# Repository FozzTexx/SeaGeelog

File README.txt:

SeaGeelog: CGA/RGBI to analog converter board
Copyright 2014 by Chris Osborn
http://insentricity.com/a.cl/219

This work is licensed under a Creative Commons Attribution-ShareAlike
4.0 International License.
http://creativecommons.org/licenses/by-sa/4.0/

This circuit is designed to convert a standard TTL level CGA/RGBI
signal to analog RGB voltages. I have tested it with the output from
my Commodore 128. It does *not* do any scan doubling or conversion to
VGA frequences. The output will still be at the CGA/RGBI frequencies
which works with old Apple or arcade monitors. I'm using a GBS-8200
clone to convert the SeaGeelog output to a VGA signal.

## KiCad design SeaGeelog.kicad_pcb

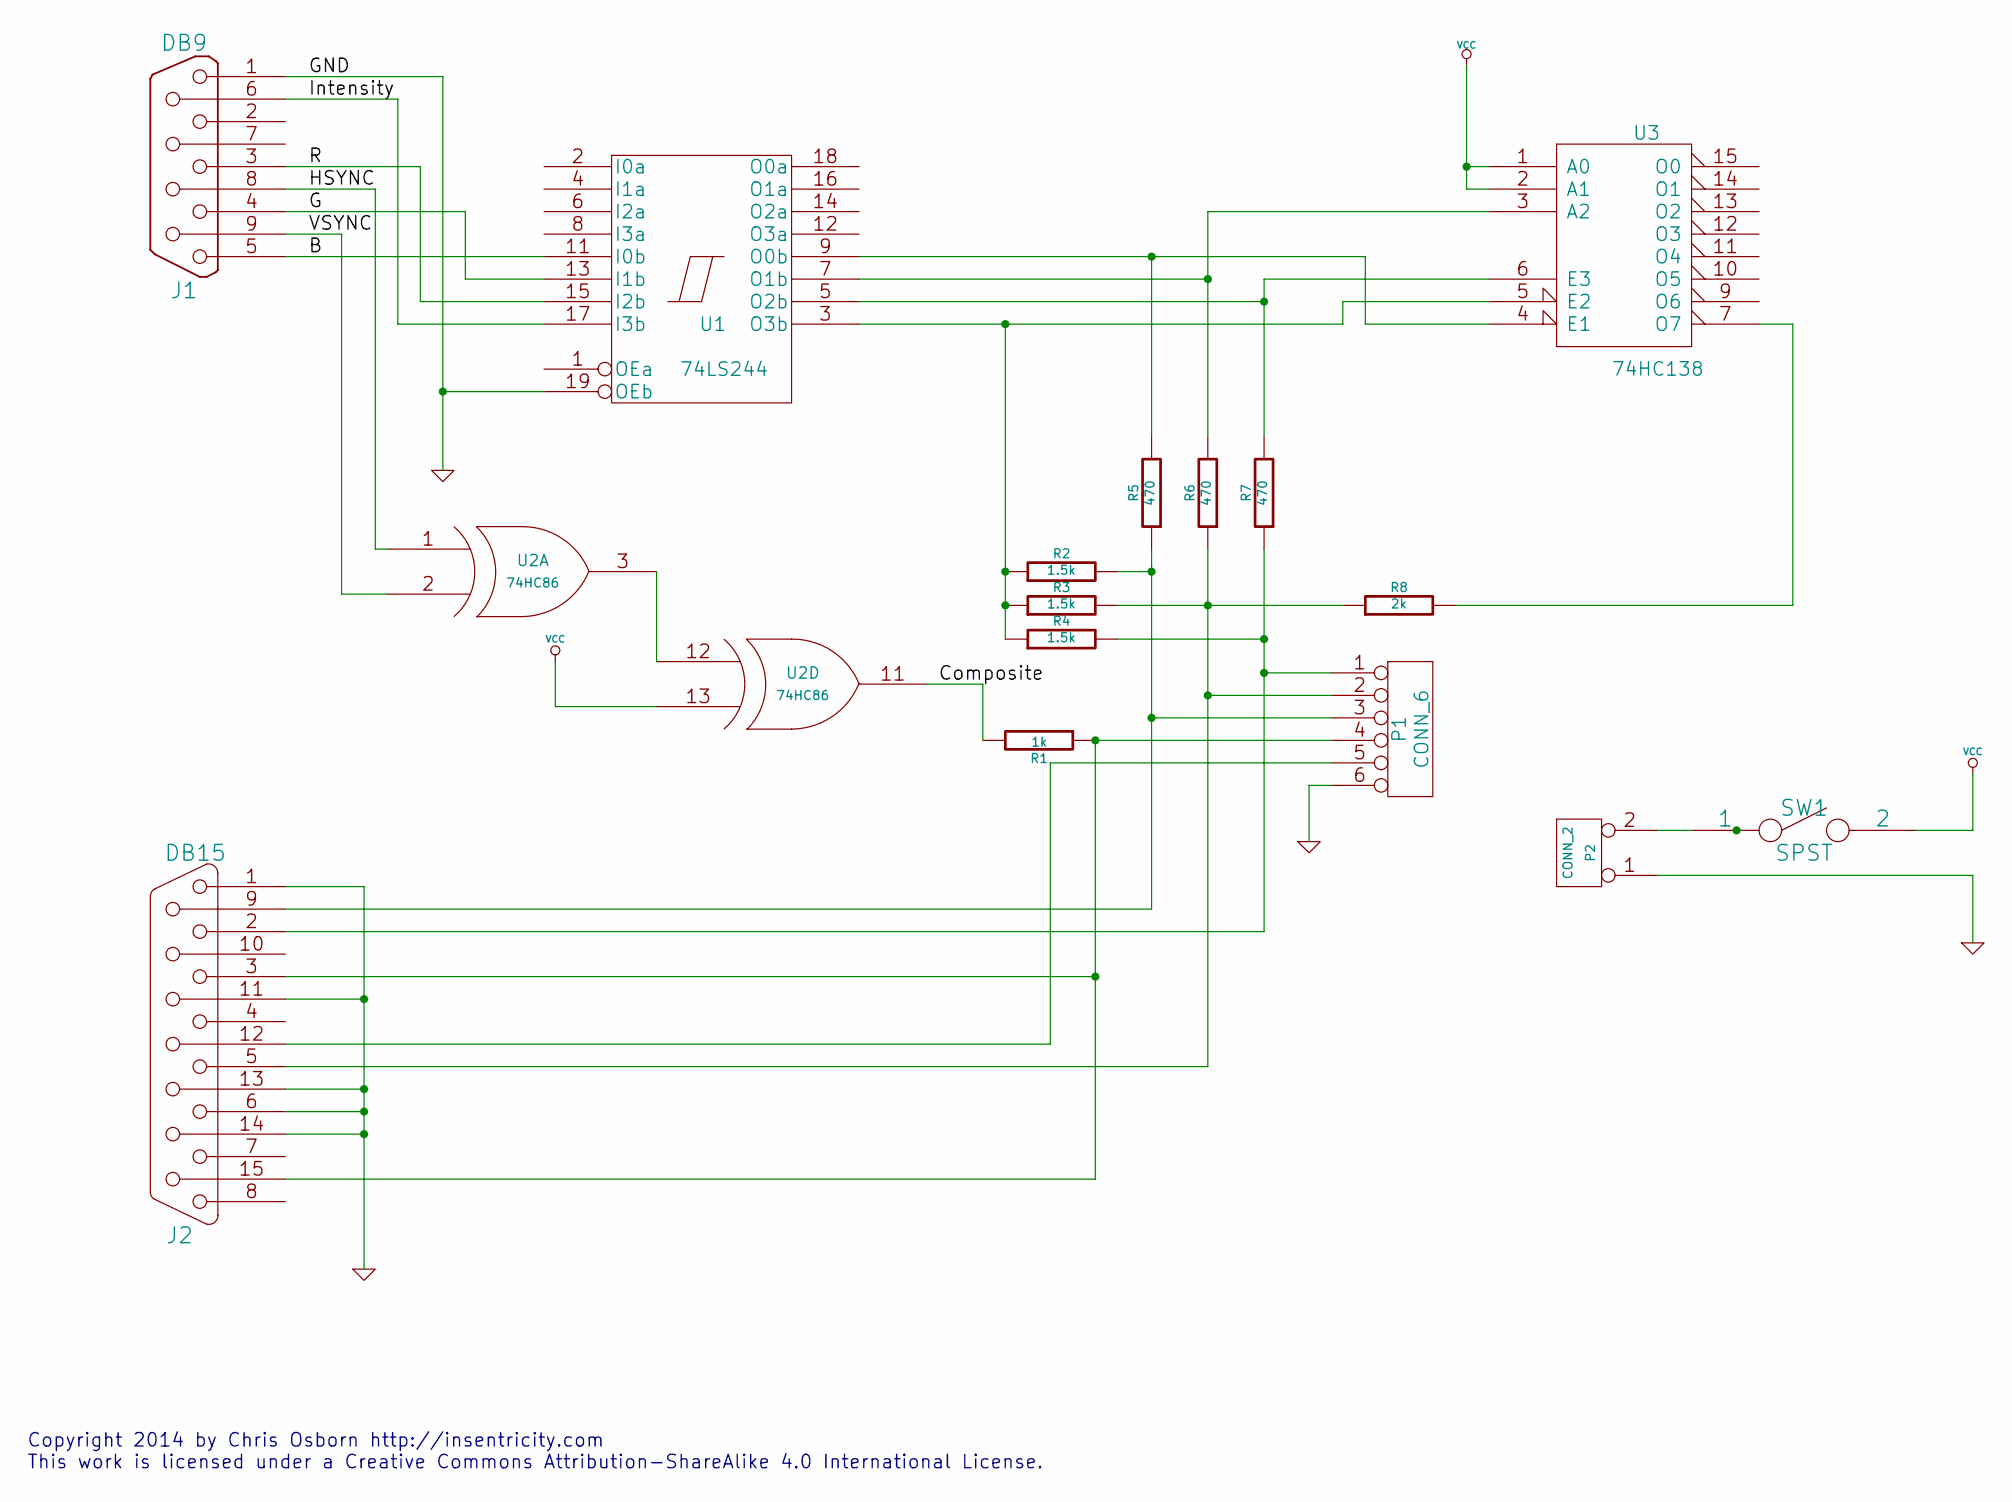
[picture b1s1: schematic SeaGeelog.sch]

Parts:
J1: DB9
J2: DB15
P1: CONN_6
P2: CONN_2
R1: 1k
R2, R3, R4: 1.5k
R5, R6, R7: 470
R8: 2k
SW1: SPST
U1: 74LS244
U2: 74HC86
U3: 74HC138

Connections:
/B: J1.5, U1.11 (I0b)
/Composite: R1.2, U2.11 (OUT)
/G: J1.4, U1.13 (I1b)
/HSYNC: J1.8, U2.1 (IN1)
/Intensity: J1.6, U1.17 (I3b)
/R: J1.3, U1.15 (I2b)
/VSYNC: J1.9, U2.2 (IN2)
GND: J1.1, J2.1, J2.6, J2.11 (P111), J2.13, J2.14, P1.6, P2.1, U1.10 (GND), U1.19 (OEb), U2.7 (GND), U3.8 (GND)
unnamed: J2.3, J2.15, P1.4, R1.1
unnamed: J2.12, P1.5
unnamed: J2.2, P1.1, R4.2, R7.1
unnamed: R8.2, U3.7 (O7)
unnamed: J2.9, P1.3, R2.2, R5.1
unnamed: J2.5, P1.2, R3.2, R6.1, R8.1
unnamed: P2.2 (PM), SW1.1
unnamed: U2.3 (OUT), U2.12 (IN1)
unnamed: R7.2, U1.5 (O2b), U3.6 (E3)
unnamed: R6.2, U1.7 (O1b), U3.3 (A2)
unnamed: R5.2, U1.9 (O0b), U3.4 (E1)
unnamed: R2.1, R3.1, R4.1, U1.3 (O3b), U3.5 (E2)
VCC: SW1.2, U1.20 (VCC), U2.13 (IN2), U2.14 (VCC), U3.1 (A0), U3.2 (A1), U3.16 (VCC)

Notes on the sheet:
Copyright 2014 by Chris Osborn http://insentricity.com This work is licensed under a Creative Commons Attribution-ShareAlike 4.0 International License.

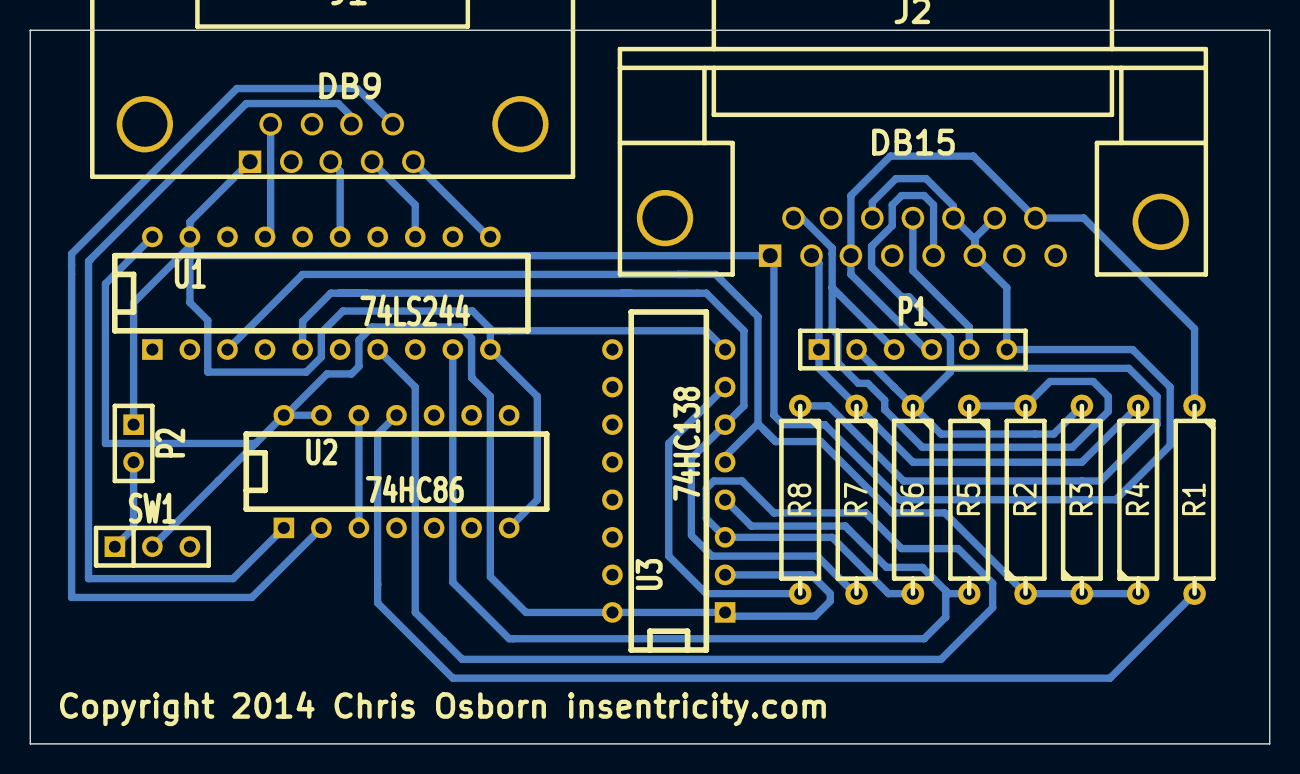
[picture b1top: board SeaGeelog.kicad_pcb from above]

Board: 2 copper layers, 83.8 x 48.3 mm, 16 parts (0 on the bottom side), 21 nets.

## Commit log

2014-03-16 First version.

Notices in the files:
SeaGeelog.kicad_pcb:
Copyright 2014 Chris Osborn insentricity.com
